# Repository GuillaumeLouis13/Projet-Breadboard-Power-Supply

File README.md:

⚡ Breadboard Power Supply

Projet de conception électronique réalisé sous KiCad dans le cadre d'une formation en ligne. Cette alimentation réglable est conçue pour fournir 3.3V et 5V à des prototypes sur plaque d'essai (breadboard), avec deux sorties de tension sélectionnables.

💡 Description du projet

Ce projet permet de convertir une tension d'entrée (12V DC via jack) en deux rails de tension stables et protégés, indispensables pour le développement de systèmes embarqués.

Caractéristiques principales :
- Entrée : Connecteur Jack DC pour alimentation secteur externe (12V).
- Régulation 5V : Basée sur le régulateur linéaire LM7805 pour une tension fixe stable.
- Régulation 3.3V : Basée sur le régulateur ajustable LM317 pour une tension précise.
 - Flexibilité : Sélecteurs de tension pour chaque rail de sortie, permettant de choisir entre 5V et 3.3V indépendamment.
- Indicateur : LED de contrôle pour visualiser immédiatement la présence d'alimentation.

🛠️ Architecture électronique
La conception a été pensée pour la simplicité et la robustesse :
- Filtrage : Condensateurs de découplage (C1, C2, C3) placés pour stabiliser les sorties et réduire le bruit des régulateurs.
- Protection : Utilisation de régulateurs linéaires standards robustes pour un prototypage sans risque.
- Ergonomie : Sorties organisées pour une connexion directe aux rails d'alimentation d'une breadboard via des connecteurs header ou borniers à vis.

📸 Aperçu du projet

Schéma électronique : 

Routage PCB : 

Conception du PCB optimisée pour le passage de courant : pistes larges pour l'alimentation et plan de masse pour la stabilité thermique.

Modèle 3D :

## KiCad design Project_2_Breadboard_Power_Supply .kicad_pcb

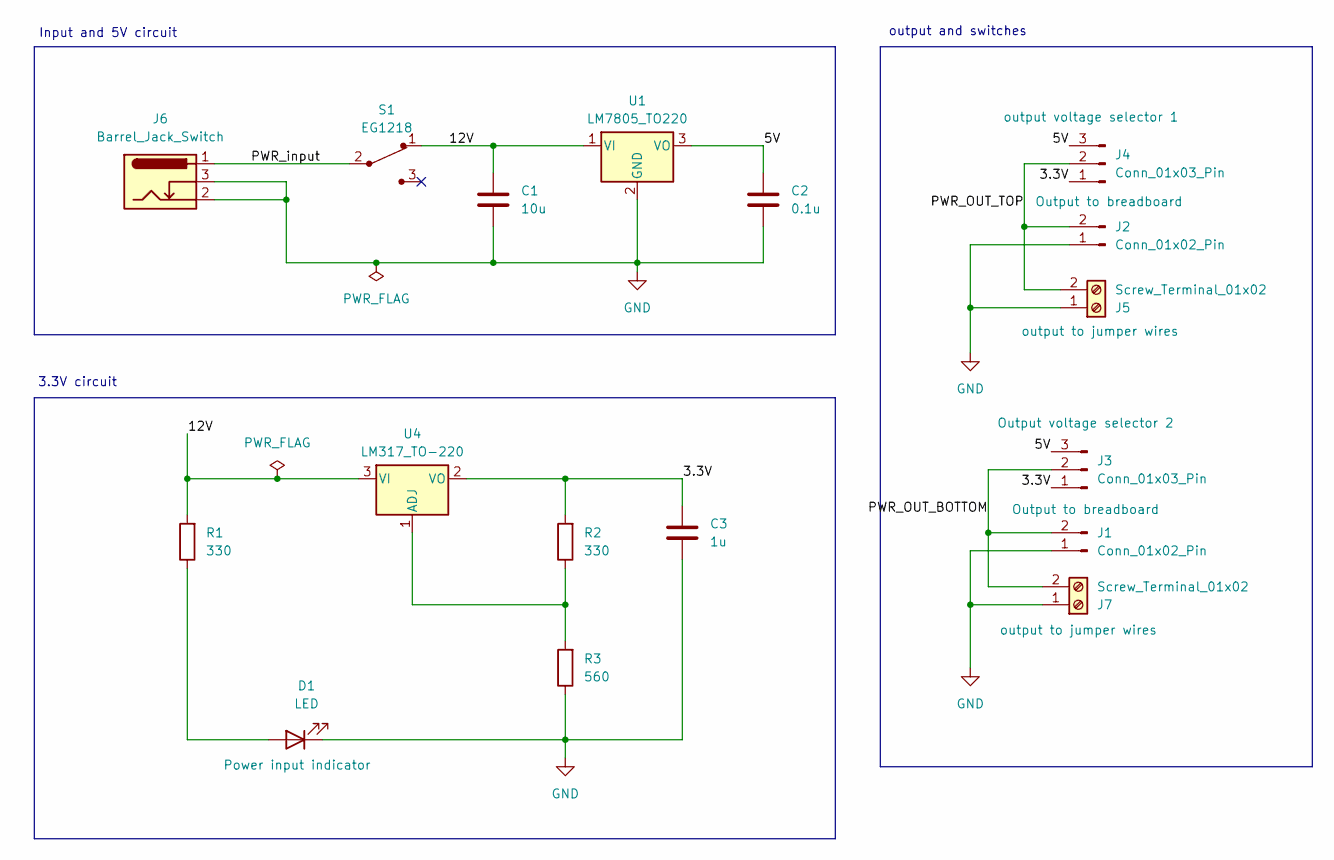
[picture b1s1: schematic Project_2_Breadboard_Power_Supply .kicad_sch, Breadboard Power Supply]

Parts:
C1: 10u; C_Disc_D3.0mm_W1.6mm_P2.50mm
C2: 0.1u; C_Disc_D3.0mm_W1.6mm_P2.50mm
C3: 1u; C_Disc_D3.0mm_W1.6mm_P2.50mm
D1: LED; LED_D5.0mm
J1, J2: Conn_01x02_Pin; PinHeader_1x02_P2.54mm_Vertical
J3, J4: Conn_01x03_Pin; PinHeader_1x03_P2.54mm_Vertical
J5, J7: Screw_Terminal_01x02; TerminalBlock_MaiXu_MX126-5.0-02P_1x02_P5.00mm
J6: Barrel_Jack_Switch; BarrelJack_Horizontal
R1, R2: 330; R_Axial_DIN0204_L3.6mm_D1.6mm_P7.62mm_Horizontal
R3: 560; R_Axial_DIN0204_L3.6mm_D1.6mm_P7.62mm_Horizontal
S1: EG1218; Switch_Slide_11.6x4mm_EG1218; MPN EG1218; Digi-Key_PN EG1903-ND
U1: LM7805_TO220; TO-220-3_Vertical
U4: LM317_TO-220; TO-220-3_Vertical

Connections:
/3.3V: C3.1, J3.1, J4.1, R2.2, U4.2 (VO)
/5V: C2.1, J3.3, J4.3, U1.3 (VO)
/12V: C1.1, R1.2, S1.1, U1.1 (VI), U4.3 (VI)
/PWR_OUT_BOTTOM: J1.2, J3.2, J7.2
/PWR_OUT_TOP: J2.2, J4.2, J5.2
/PWR_input: J6.1, S1.2
GND: C1.2, C2.2, C3.2, D1.1 (K), J1.1, J2.1, J5.1, J6.2, J6.3, J7.1, R3.1, U1.2 (GND)
unnamed: D1.2 (A), R1.1
unnamed: R2.1, R3.2, U4.1 (ADJ)

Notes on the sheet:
3.3V circuit
Input and 5V circuit
output and switches

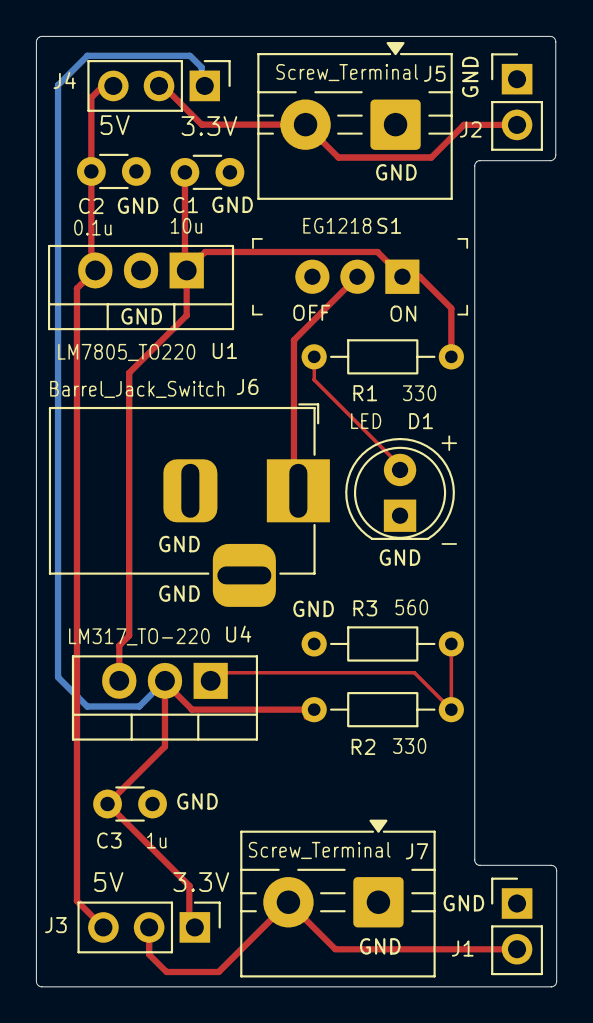
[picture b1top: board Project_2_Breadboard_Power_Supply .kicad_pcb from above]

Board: 2 copper layers, 28.9 x 52.8 mm, 17 parts (0 on the bottom side), 9 nets.

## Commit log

2026-05-24 commit du projet Breadboard Power Supply
2026-05-24 suppression du fichier cat
2026-05-24 amelioration gitignore
2026-05-24 ajout photos et gestion gitignore
2026-05-24 commit de changements mineurs pcb
2026-05-24 Modification des images
